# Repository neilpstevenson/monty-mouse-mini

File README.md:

# monty-mouse-mini
Source code for micromouse Monty Mini

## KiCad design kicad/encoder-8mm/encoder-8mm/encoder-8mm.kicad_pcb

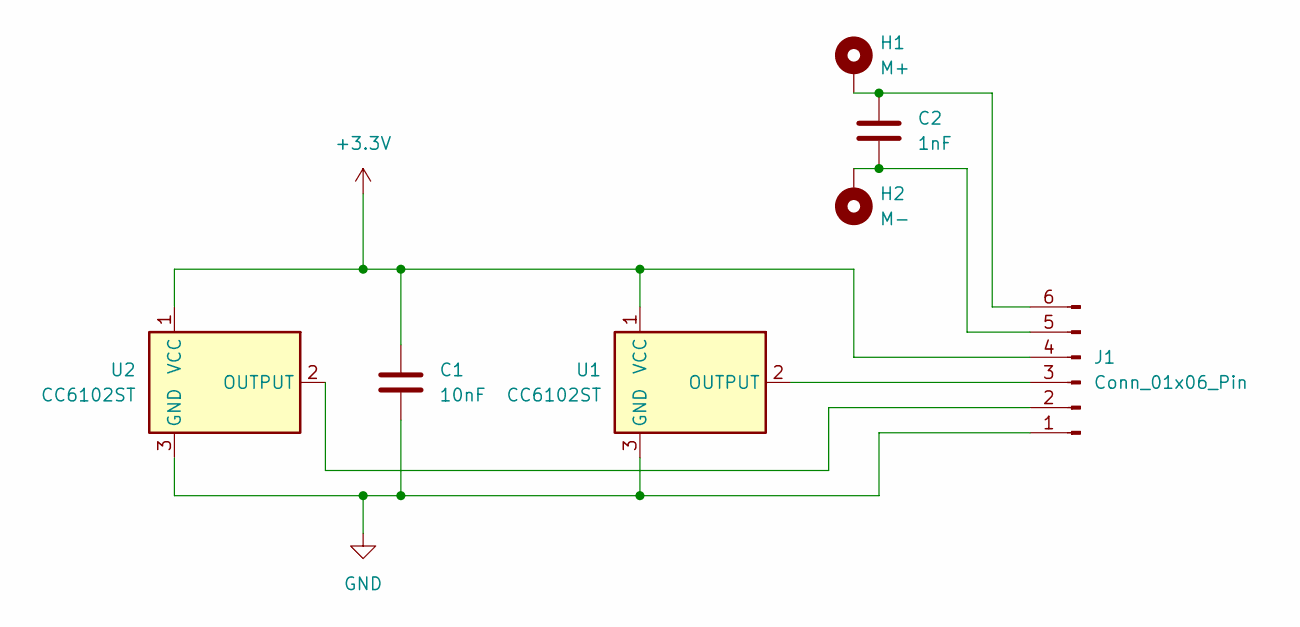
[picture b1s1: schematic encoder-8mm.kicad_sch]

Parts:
C1: 10nF; C_0805_2012Metric
C2: 1nF; C_0805_2012Metric
H1: M+; small_slot_1.2x0.3mm
H2: M-; small_slot_1.2x0.3mm
J1: Conn_01x06_Pin; PinSocket_1x06_P1.00mm_Vertical
U1, U2: CC6102ST; SOT-23

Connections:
+3.3V: C1.1, J1.4, U1.1 (VCC), U2.1 (VCC)
GND: C1.2, J1.1, U1.3 (GND), U2.3 (GND)
unnamed: J1.2, U2.2 (OUTPUT)
unnamed: J1.3, U1.2 (OUTPUT)
unnamed: C2.2, H2.1, J1.5
unnamed: C2.1, H1.1, J1.6

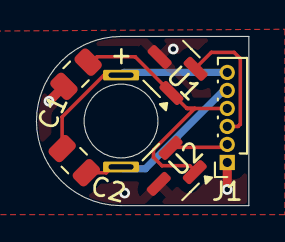
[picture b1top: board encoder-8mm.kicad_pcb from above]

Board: 2 copper layers, 11.8 x 9.4 mm, 7 parts (0 on the bottom side), 6 nets.

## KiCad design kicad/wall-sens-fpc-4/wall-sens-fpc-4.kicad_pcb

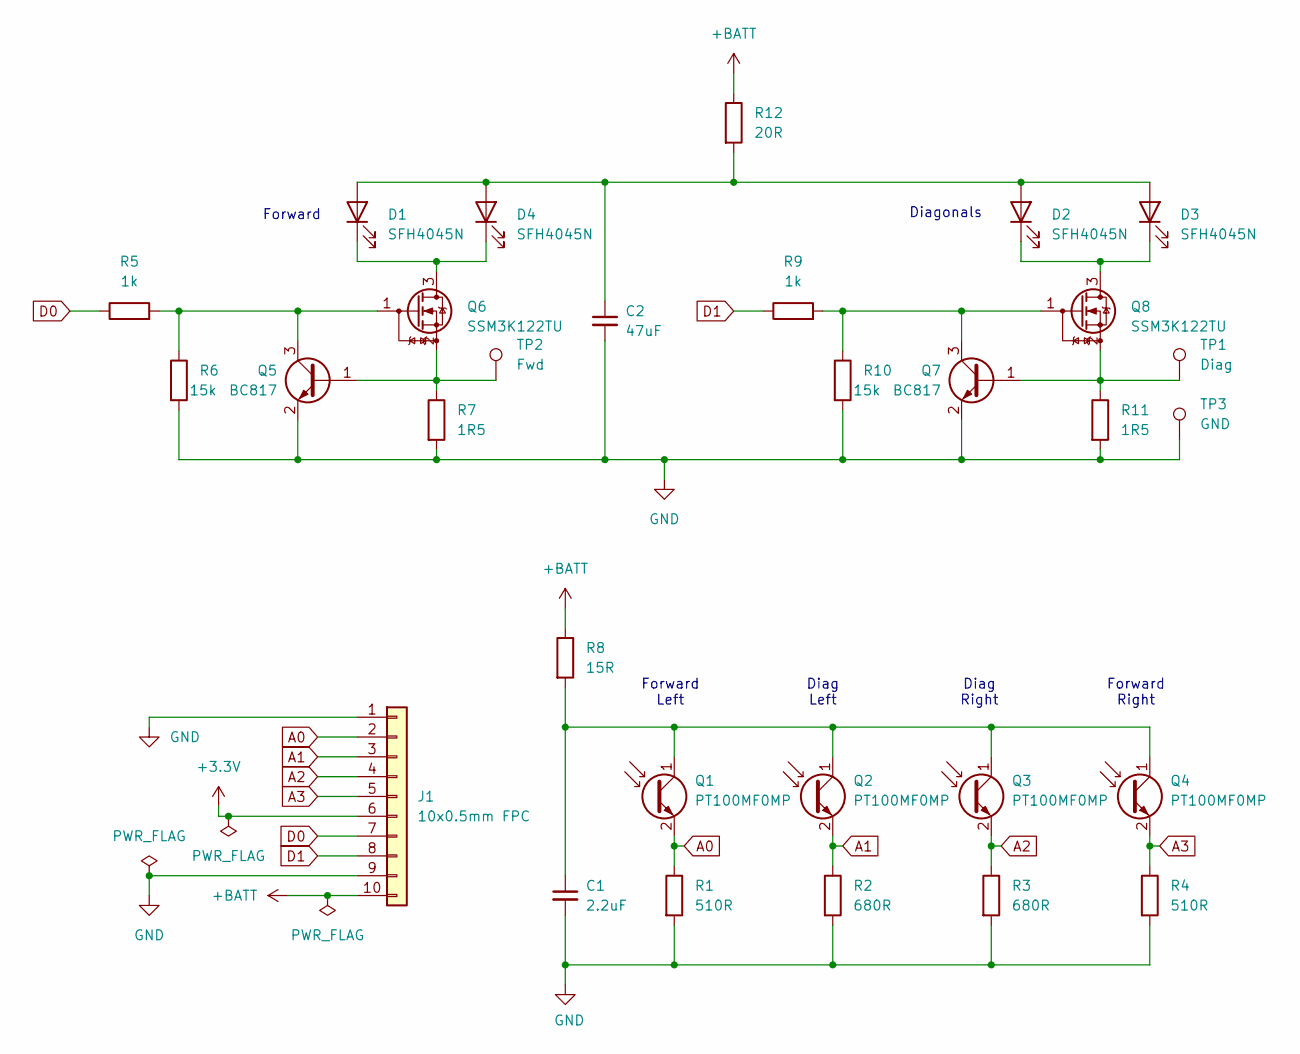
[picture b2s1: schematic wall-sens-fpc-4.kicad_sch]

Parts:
C1: 2.2uF; C_0805_2012Metric
C2: 47uF; C_1206_3216Metric
D1, D2, D3, D4: SFH4045N; LED_SFH_4045N
J1: 10x0.5mm FPC; SlimFPC_1x10-1MP_P0.5mm_Horizontal_ExtPads
Q1, Q2, Q3, Q4: PT100MF0MP; PT100_SHP_H
Q5, Q7: BC817; SOT-23
Q6, Q8: SSM3K122TU; UFM_TOS-M
R1, R4: 510R; R_0805_2012Metric
R2, R3: 680R; R_0805_2012Metric
R5, R9: 1k; R_0805_2012Metric
R6, R10: 15k; R_0805_2012Metric
R7, R11: 1R5; R_0805_2012Metric
R8: 15R; R_0805_2012Metric
R12: 20R; R_0805_2012Metric
TP1: Diag; TestPoint_Pad_D1.5mm
TP2: Fwd; TestPoint_Pad_D1.5mm
TP3: GND; TestPoint_THTPad_1.5x1.5mm_Drill0.7mm

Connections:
+3.3V: J1.6
+BATT: J1.10, R8.1, R12.1
A0: J1.2, Q1.2 (E), R1.1
A1: J1.3, Q2.2 (E), R2.1
A2: J1.4, Q3.2 (E), R3.1
A3: J1.5, Q4.2 (E), R4.1
D0: J1.7, R5.1
D1: J1.8, R9.1
GND: C1.2, C2.2, J1.1, J1.9, Q5.2 (E), Q7.2 (E), R1.2, R2.2, R3.2, R4.2, R6.2, R7.2, R10.2, R11.2, TP3.1
unnamed: C2.1, D1.2 (A), D2.2 (A), D3.2 (A), D4.2 (A), R12.2
unnamed: D1.1 (K), D4.1 (K), Q6.3 (D)
unnamed: D2.1 (K), D3.1 (K), Q8.3 (D)
unnamed: C1.1, Q1.1 (C), Q2.1 (C), Q3.1 (C), Q4.1 (C), R8.2
unnamed: Q5.1 (B), Q6.2 (S), R7.1, TP2.1
unnamed: Q5.3 (C), Q6.1 (G), R5.2, R6.1
unnamed: Q7.1 (B), Q8.2 (S), R11.1, TP1.1
unnamed: Q7.3 (C), Q8.1 (G), R9.2, R10.1

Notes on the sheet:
Forward Left
Diag Right
Diag Left
Diagonals
Forward
Forward Right

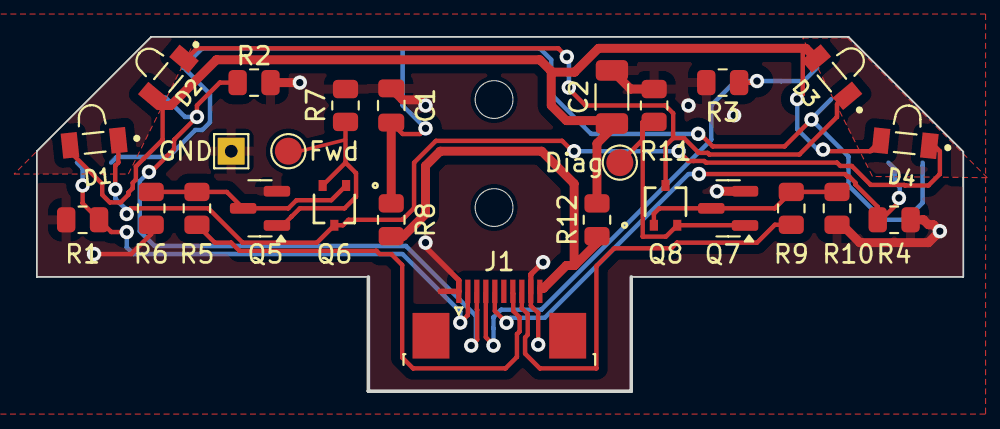
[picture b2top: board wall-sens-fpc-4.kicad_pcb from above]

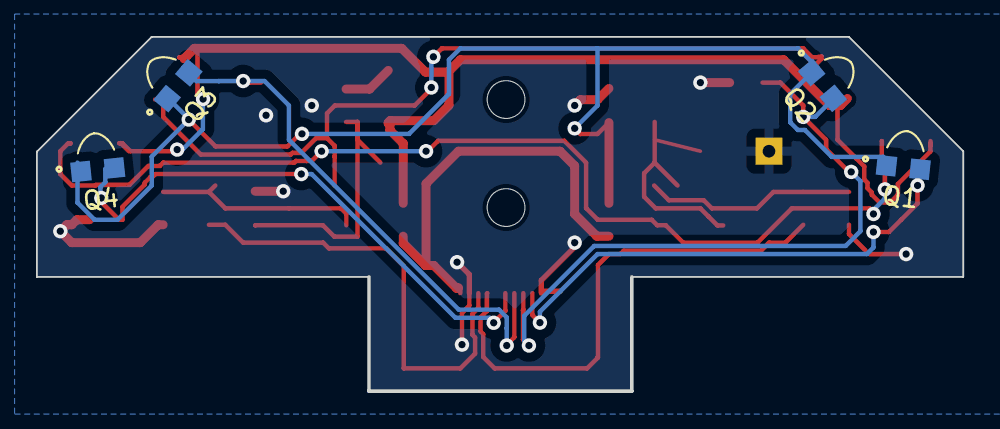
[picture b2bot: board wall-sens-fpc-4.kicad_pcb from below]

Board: 2 copper layers, 51.4 x 19.6 mm, 32 parts (4 on the bottom side), 16 nets.

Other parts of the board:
REF-mh: MountingHole_2.1mm
REF-mh#2: MountingHole_2.1mm

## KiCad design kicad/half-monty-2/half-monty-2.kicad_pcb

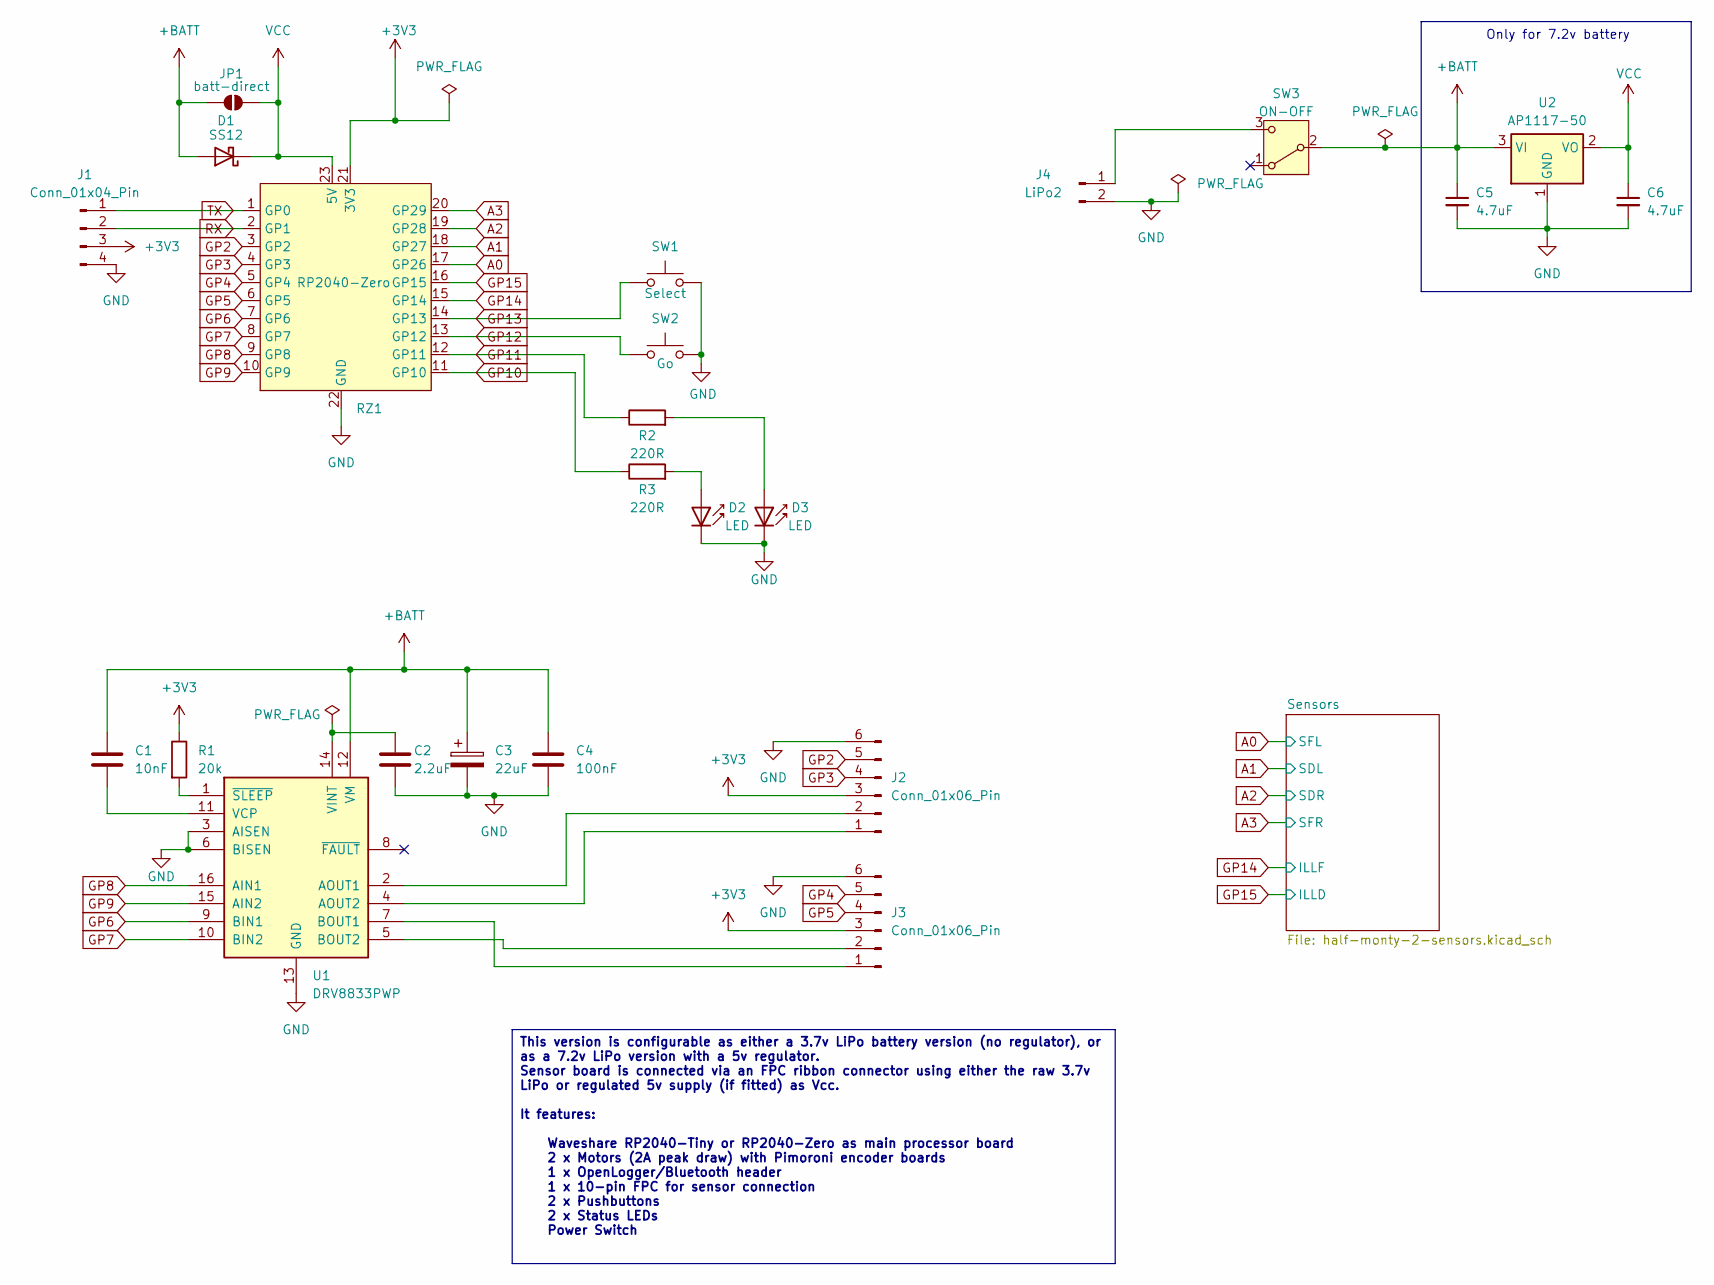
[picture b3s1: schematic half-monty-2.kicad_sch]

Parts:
C1: 10nF; C_0805_2012Metric
C2: 2.2uF; C_0805_2012Metric
C3: 22uF; C_0805_2012Metric
C4: 100nF; C_0805_2012Metric
C5, C6: 4.7uF; C_0805_2012Metric_Pad1.18x1.45mm_HandSolder
D1: SS12; D_SMA
D2, D3: LED; LED_1206_3216Metric
J1: Conn_01x04_Pin; PinHeader_1x04_P2.54mm_Vertical
J2, J3: Conn_01x06_Pin; JST_SH_SM06B-SRSS-TB_1x06-1MP_P1.00mm_Horizontal
J4: LiPo2; PinHeader_1x02_P1.27mm_Vertical
JP1: batt-direct; SolderJumper-2_P1.3mm_Open_Pad1.0x1.5mm
R1: 20k; R_0805_2012Metric
R2, R3: 220R; R_0805_2012Metric
RZ1: RP2040-Zero; RP2040-Zero-outline-THP
SW1: Select; SW_SPST_CK_RS282G05A3
SW2: Go; SW_SPST_CK_RS282G05A3
SW3: ON-OFF; SW_SPDT_PCM12_VERT
U1: DRV8833PWP; HTSSOP-16-1EP_4.4x5mm_P0.65mm_EP3.4x5mm_Mask2.46x2.31mm_The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
U2: AP1117-50; SOT-223-3_TabPin2

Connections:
+3V3: J1.3, J2.3, J3.3, R1.1, RZ1.21 (3V3)
+BATT: C1.1, C3.1, C4.1, C5.1, D1.2 (A), JP1.1 (A), SW3.2 (B), U1.12 (VM), U2.3 (VI); also elsewhere on the board
A0: RZ1.17 (GP26); also elsewhere on the board
A1: RZ1.18 (GP27); also elsewhere on the board
A2: RZ1.19 (GP28); also elsewhere on the board
A3: RZ1.20 (GP29); also elsewhere on the board
GND: C2.1, C3.2, C4.2, C5.2, C6.2, D2.1 (K), D3.1 (K), J1.4, J2.6, J3.6, J4.2, RZ1.22 (GND), SW1.2, SW2.2, U1.3 (AISEN), U1.6 (BISEN), U1.13 (GND), U1.17 (GND), U2.1 (GND); also elsewhere on the board
GP2: J2.5, RZ1.3 (GP2)
GP3: J2.4, RZ1.4 (GP3)
GP4: J3.5, RZ1.5 (GP4)
GP5: J3.4, RZ1.6 (GP5)
GP6: RZ1.7 (GP6), U1.9 (BIN1)
GP7: RZ1.8 (GP7), U1.10 (BIN2)
GP8: RZ1.9 (GP8), U1.16 (AIN1)
GP9: RZ1.10 (GP9), U1.15 (AIN2)
GP10: R3.1, RZ1.11 (GP10)
GP11: R2.1, RZ1.12 (GP11)
GP12: RZ1.13 (GP12), SW2.1
GP13: RZ1.14 (GP13), SW1.1
GP14: RZ1.15 (GP14); also elsewhere on the board
GP15: RZ1.16 (GP15); also elsewhere on the board
unnamed: D2.2 (A), R3.2
unnamed: D3.2 (A), R2.2
unnamed: J2.1, U1.4 (AOUT2)
unnamed: J2.2, U1.2 (AOUT1)
unnamed: J3.1, U1.7 (BOUT1)
unnamed: J3.2, U1.5 (BOUT2)
unnamed: J4.1, SW3.3 (C)
unnamed: C1.2, U1.11 (VCP)
unnamed: C2.2, U1.14 (VINT)
unnamed: R1.2, U1.1 (~SLEEP)
RX: J1.2, RZ1.2 (GP1)
TX: J1.1, RZ1.1 (GP0)
VCC: C6.1, D1.1 (K), JP1.2 (B), RZ1.23 (5V), U2.2 (VO)

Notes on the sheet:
Only for 7.2v battery
This version is configurable as either a 3.7v LiPo battery version (no regulator), or as a 7.2v LiPo version with a 5v regulator. Sensor board is connected via an FPC ribbon connector using either the raw 3.7v LiPo or regulated 5v supply (if fitted) as Vcc. It features: Waveshare RP2040-Tiny or RP2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

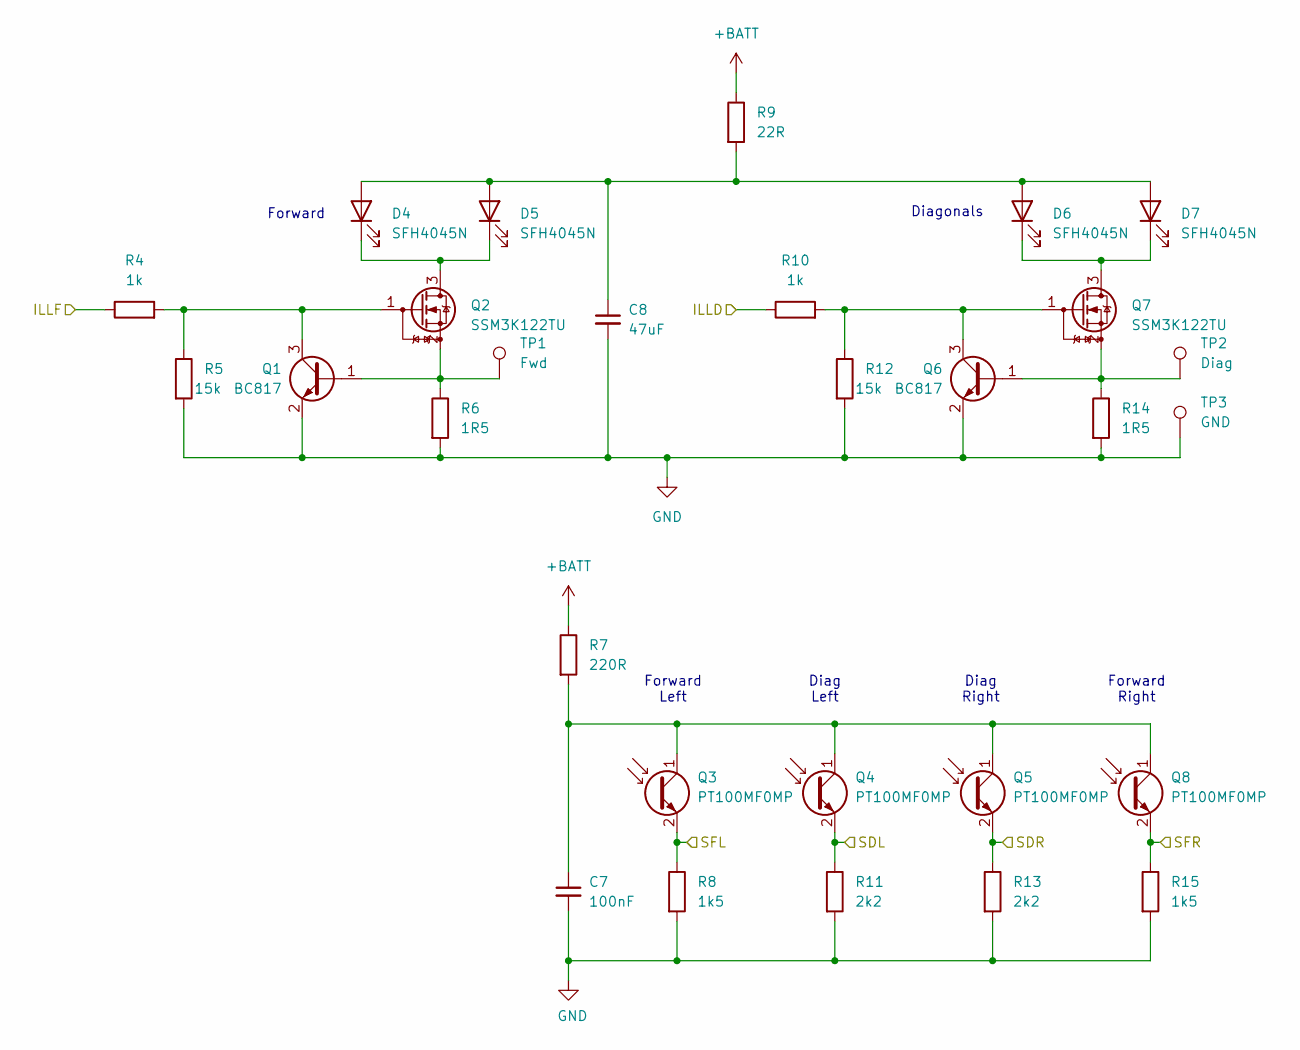
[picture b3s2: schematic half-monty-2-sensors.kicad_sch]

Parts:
C7: 100nF; C_0805_2012Metric
C8: 47uF; C_1206_3216Metric
D4, D5, D6, D7: SFH4045N; LED_SFH_4045N
Q1, Q6: BC817; SOT-23
Q2, Q7: SSM3K122TU; UFM_TOS-M
Q3, Q4, Q5, Q8: PT100MF0MP; PT100_SHP_H
R4, R10: 1k; R_0805_2012Metric
R5, R12: 15k; R_0805_2012Metric
R6, R14: 1R5; R_0805_2012Metric
R7: 220R; R_0805_2012Metric
R8, R15: 1k5; R_0805_2012Metric
R9: 22R; R_0805_2012Metric
R11, R13: 2k2; R_0805_2012Metric
TP1: Fwd; TestPoint_Pad_D1.5mm
TP2: Diag; TestPoint_Pad_D1.5mm
TP3: GND; TestPoint_THTPad_1.5x1.5mm_Drill0.7mm

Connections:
+BATT: R7.1, R9.1; also elsewhere on the board
A0: Q3.2 (E), R8.1; also elsewhere on the board
A1: Q4.2 (E), R11.1; also elsewhere on the board
A2: Q5.2 (E), R13.1; also elsewhere on the board
A3: Q8.2 (E), R15.1; also elsewhere on the board
GND: C7.2, C8.2, Q1.2 (E), Q6.2 (E), R5.2, R6.2, R8.2, R11.2, R12.2, R13.2, R14.2, R15.2, TP3.1; also elsewhere on the board
GP14: R4.1; also elsewhere on the board
GP15: R10.1; also elsewhere on the board
unnamed: C8.1, D4.2 (A), D5.2 (A), D6.2 (A), D7.2 (A), R9.2
unnamed: D4.1 (K), D5.1 (K), Q2.3 (D)
unnamed: D6.1 (K), D7.1 (K), Q7.3 (D)
unnamed: Q1.1 (B), Q2.2 (S), R6.1, TP1.1
unnamed: Q1.3 (C), Q2.1 (G), R4.2, R5.1
unnamed: C7.1, Q3.1 (C), Q4.1 (C), Q5.1 (C), Q8.1 (C), R7.2
unnamed: Q6.1 (B), Q7.2 (S), R14.1, TP2.1
unnamed: Q6.3 (C), Q7.1 (G), R10.2, R12.1

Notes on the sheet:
Diagonals
Forward
Forward Left
Diag Right
Forward Right
Diag Left

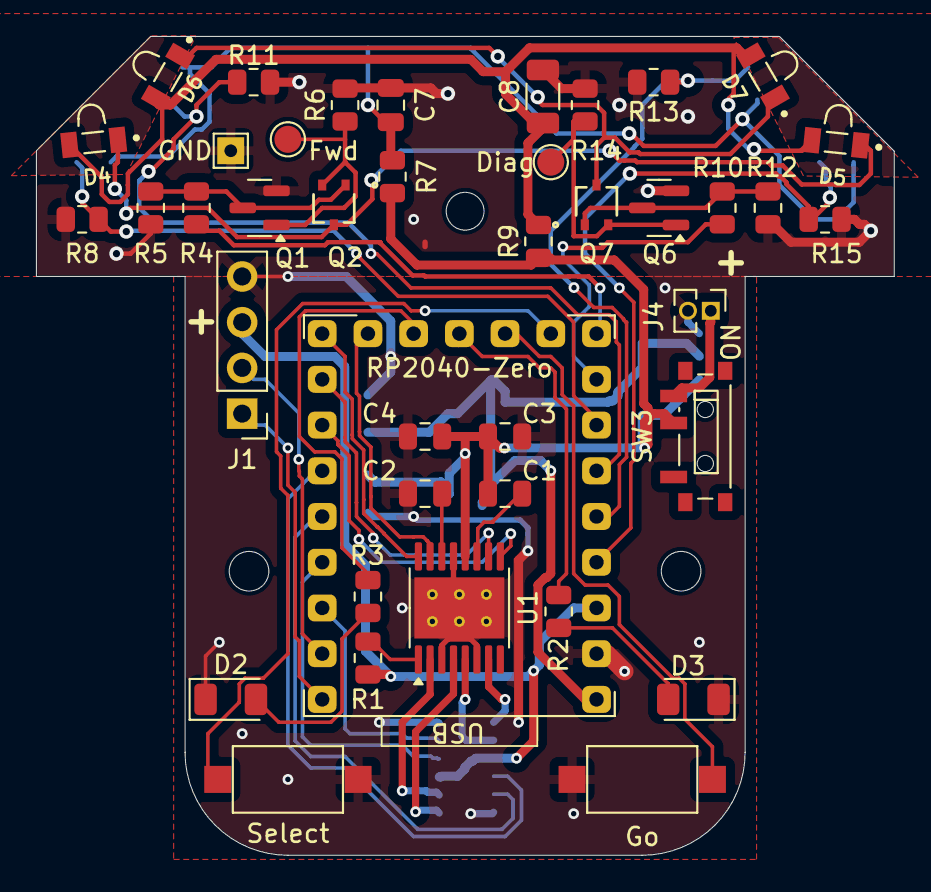
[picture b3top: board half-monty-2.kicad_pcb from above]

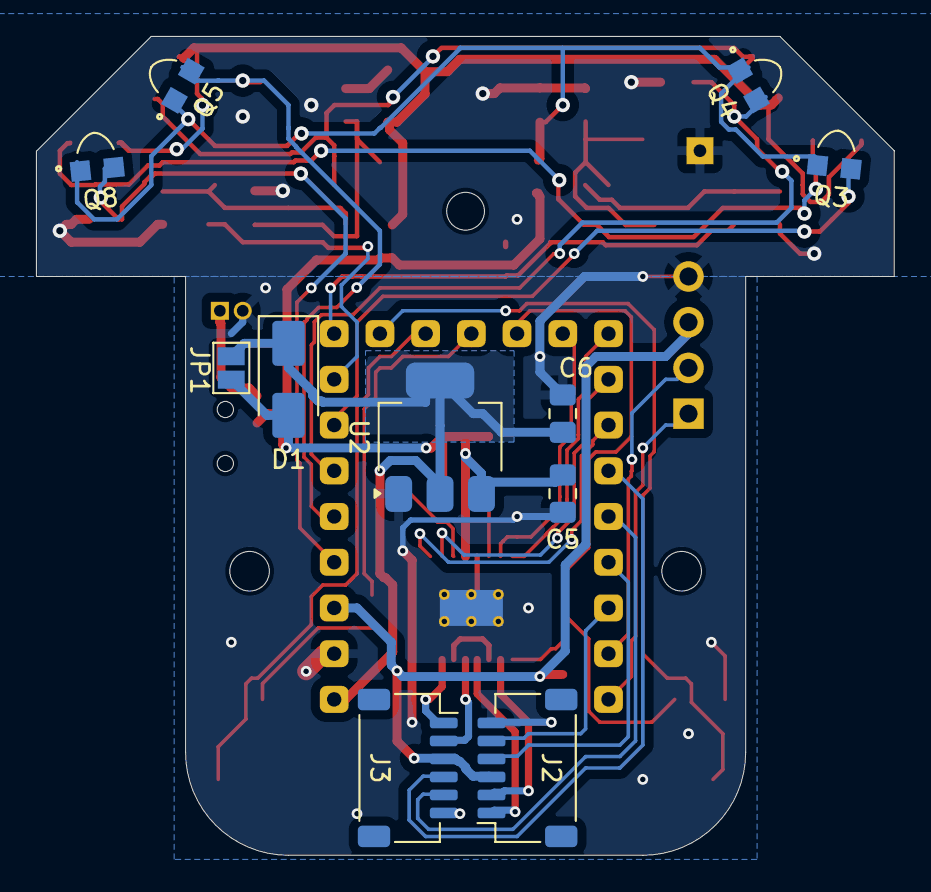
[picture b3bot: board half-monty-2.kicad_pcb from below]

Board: 2 copper layers, 47.7 x 45.5 mm, 53 parts (11 on the bottom side), 42 nets.

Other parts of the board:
REF-mh: MountingHole_2.1mm

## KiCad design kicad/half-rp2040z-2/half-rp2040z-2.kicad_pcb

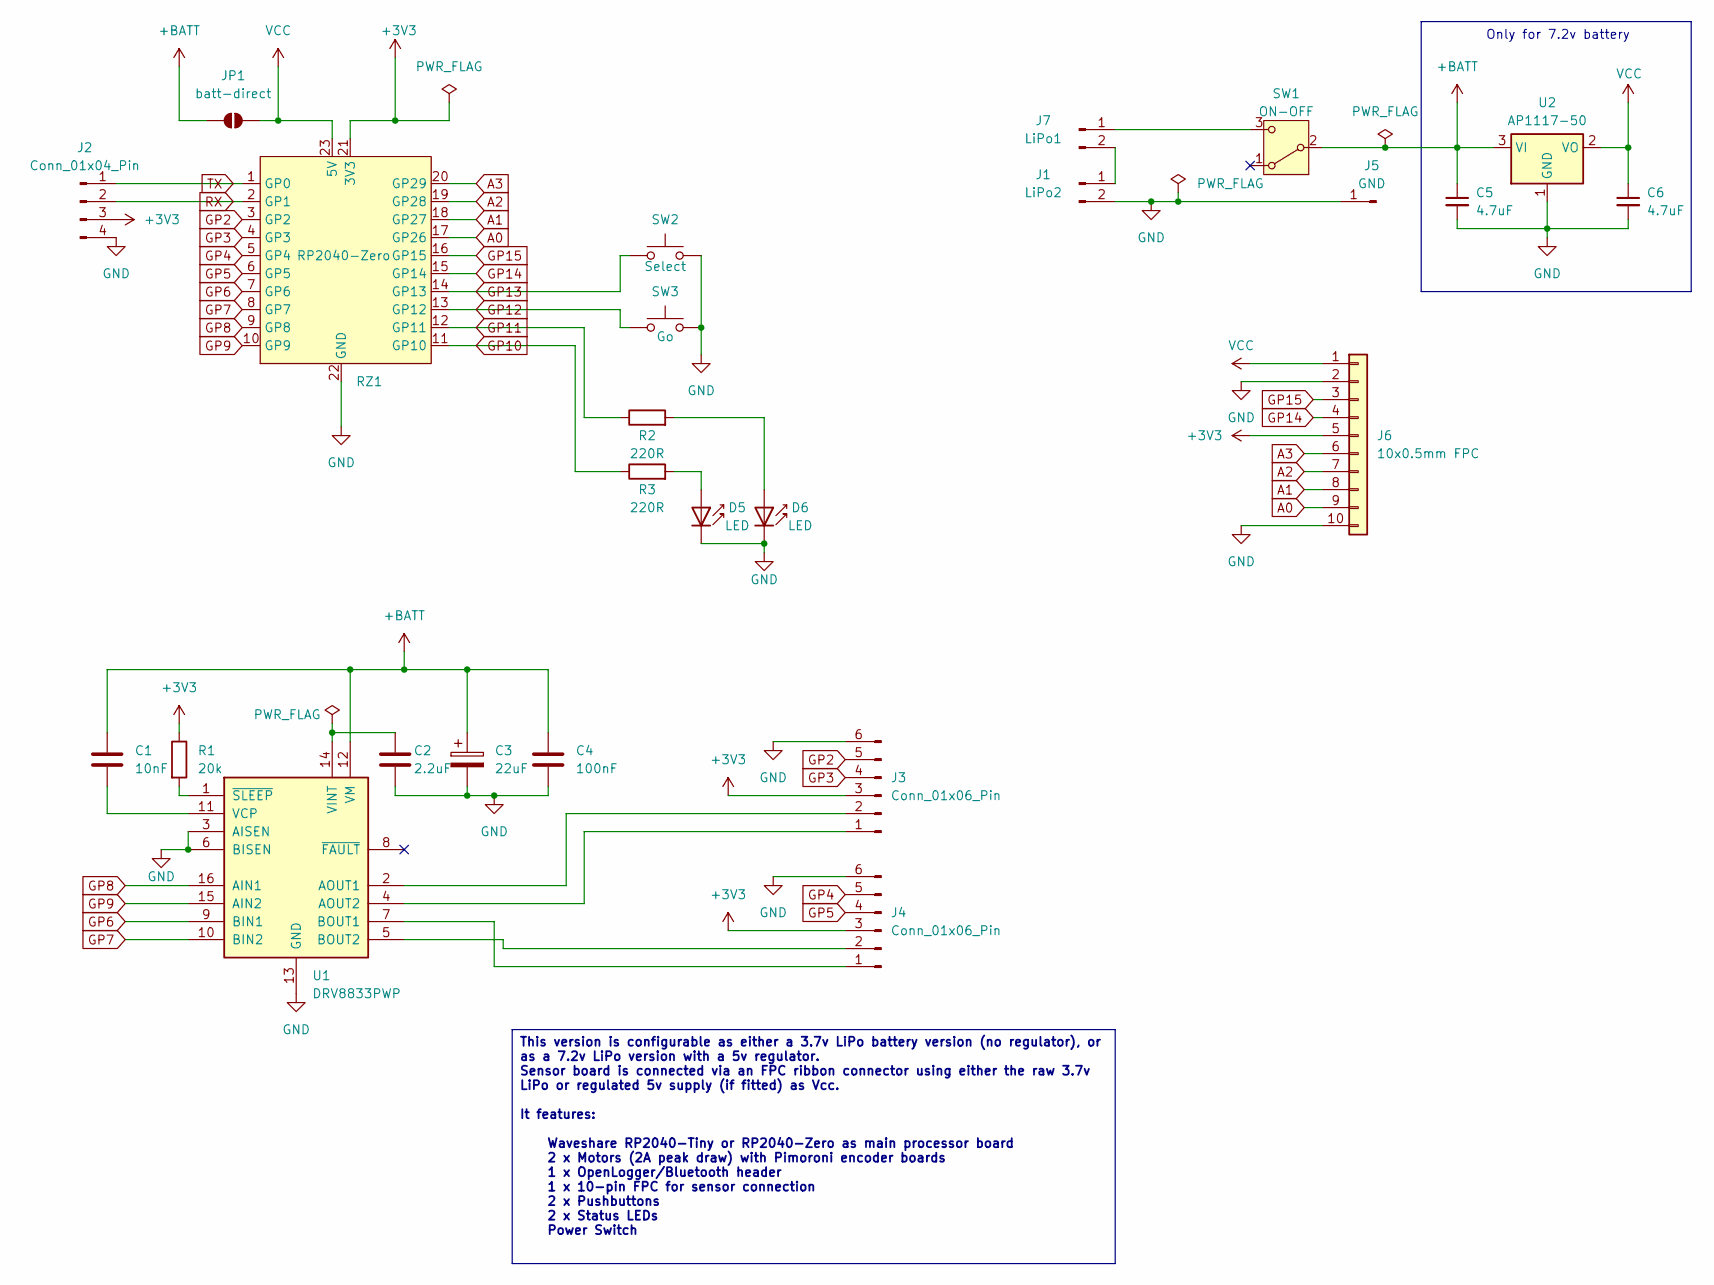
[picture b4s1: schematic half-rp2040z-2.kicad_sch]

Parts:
C1: 10nF; C_0805_2012Metric
C2: 2.2uF; C_0805_2012Metric
C3: 22uF; C_0805_2012Metric
C4: 100nF; C_0805_2012Metric
C5, C6: 4.7uF; C_0805_2012Metric_Pad1.18x1.45mm_HandSolder
D5, D6: LED; LED_1206_3216Metric
J1: LiPo2; PinHeader_1x02_P1.27mm_Vertical
J2: Conn_01x04_Pin; PinHeader_1x04_P2.54mm_Vertical
J3, J4: Conn_01x06_Pin; JST_SH_SM06B-SRSS-TB_1x06-1MP_P1.00mm_Horizontal
J5: GND; PinHeader_1x01_P2.54mm_Vertical
J6: 10x0.5mm FPC; SlimFPC_1x10-1MP_P0.5mm_Horizontal_ExtPads
J7: LiPo1; PinHeader_1x02_P1.27mm_Vertical
JP1: batt-direct; SolderJumper-2_P1.3mm_Open_Pad1.0x1.5mm
R1: 20k; R_0805_2012Metric
R2, R3: 220R; R_0805_2012Metric
RZ1: RP2040-Zero; RP2040-Zero-outline-THP
SW1: ON-OFF; SW_SPDT_PCM12_VERT
SW2: Select; SW_SPST_CK_RS282G05A3
SW3: Go; SW_SPST_CK_RS282G05A3
U1: DRV8833PWP; HTSSOP-16-1EP_4.4x5mm_P0.65mm_EP3.4x5mm_Mask2.46x2.31mm_The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
U2: AP1117-50; SOT-223-3_TabPin2

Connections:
+3V3: J2.3, J3.3, J4.3, J6.5, R1.1, RZ1.21 (3V3)
+BATT: C1.1, C3.1, C4.1, C5.1, JP1.1 (A), SW1.2 (B), U1.12 (VM), U2.3 (VI)
A0: J6.9, RZ1.17 (GP26)
A1: J6.8, RZ1.18 (GP27)
A2: J6.7, RZ1.19 (GP28)
A3: J6.6, RZ1.20 (GP29)
GND: C2.1, C3.2, C4.2, C5.2, C6.2, D5.1 (K), D6.1 (K), J1.2, J2.4, J3.6, J4.6, J5.1, J6.2, J6.10, RZ1.22 (GND), SW2.2, SW3.2, U1.3 (AISEN), U1.6 (BISEN), U1.13 (GND), U1.17 (GND), U2.1 (GND)
GP2: J3.5, RZ1.3 (GP2)
GP3: J3.4, RZ1.4 (GP3)
GP4: J4.5, RZ1.5 (GP4)
GP5: J4.4, RZ1.6 (GP5)
GP6: RZ1.7 (GP6), U1.9 (BIN1)
GP7: RZ1.8 (GP7), U1.10 (BIN2)
GP8: RZ1.9 (GP8), U1.16 (AIN1)
GP9: RZ1.10 (GP9), U1.15 (AIN2)
GP10: R3.1, RZ1.11 (GP10)
GP11: R2.1, RZ1.12 (GP11)
GP12: RZ1.13 (GP12), SW3.1
GP13: RZ1.14 (GP13), SW2.1
GP14: J6.4, RZ1.15 (GP14)
GP15: J6.3, RZ1.16 (GP15)
unnamed: D5.2 (A), R3.2
unnamed: D6.2 (A), R2.2
unnamed: J1.1, J7.2
unnamed: J3.1, U1.4 (AOUT2)
unnamed: J3.2, U1.2 (AOUT1)
unnamed: J4.1, U1.7 (BOUT1)
unnamed: J4.2, U1.5 (BOUT2)
unnamed: J7.1, SW1.3 (C)
unnamed: C1.2, U1.11 (VCP)
unnamed: C2.2, U1.14 (VINT)
unnamed: R1.2, U1.1 (~SLEEP)
RX: J2.2, RZ1.2 (GP1)
TX: J2.1, RZ1.1 (GP0)
VCC: C6.1, J6.1, JP1.2 (B), RZ1.23 (5V), U2.2 (VO)

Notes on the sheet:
Only for 7.2v battery
This version is configurable as either a 3.7v LiPo battery version (no regulator), or as a 7.2v LiPo version with a 5v regulator. Sensor board is connected via an FPC ribbon connector using either the raw 3.7v LiPo or regulated 5v supply (if fitted) as Vcc. It features: Waveshare RP2040-Tiny or RP2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

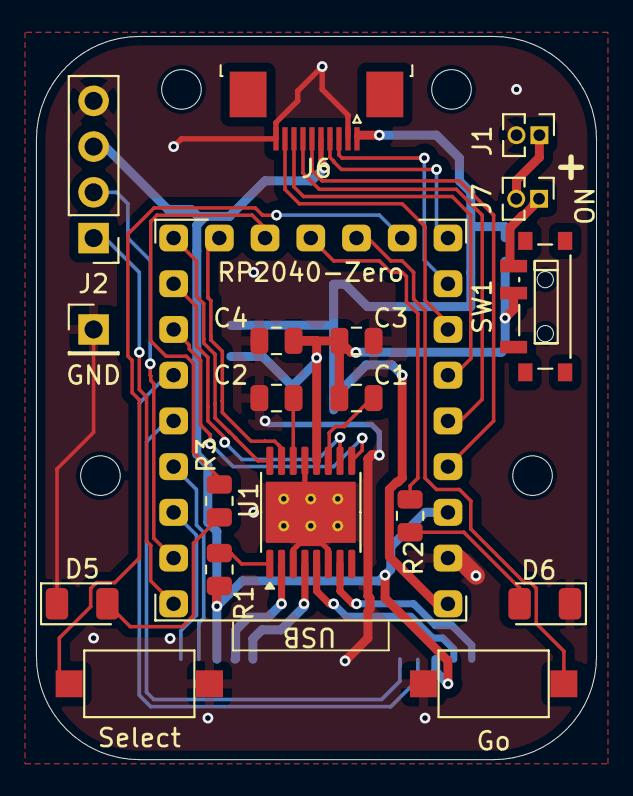
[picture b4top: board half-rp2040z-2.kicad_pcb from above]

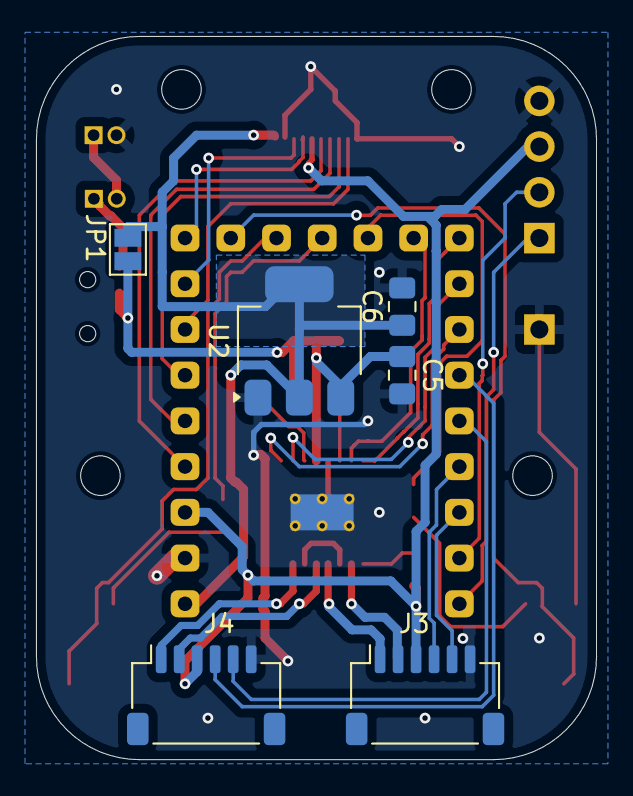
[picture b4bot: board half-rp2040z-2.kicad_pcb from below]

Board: 2 copper layers, 31.1 x 40.2 mm, 25 parts (6 on the bottom side), 35 nets.

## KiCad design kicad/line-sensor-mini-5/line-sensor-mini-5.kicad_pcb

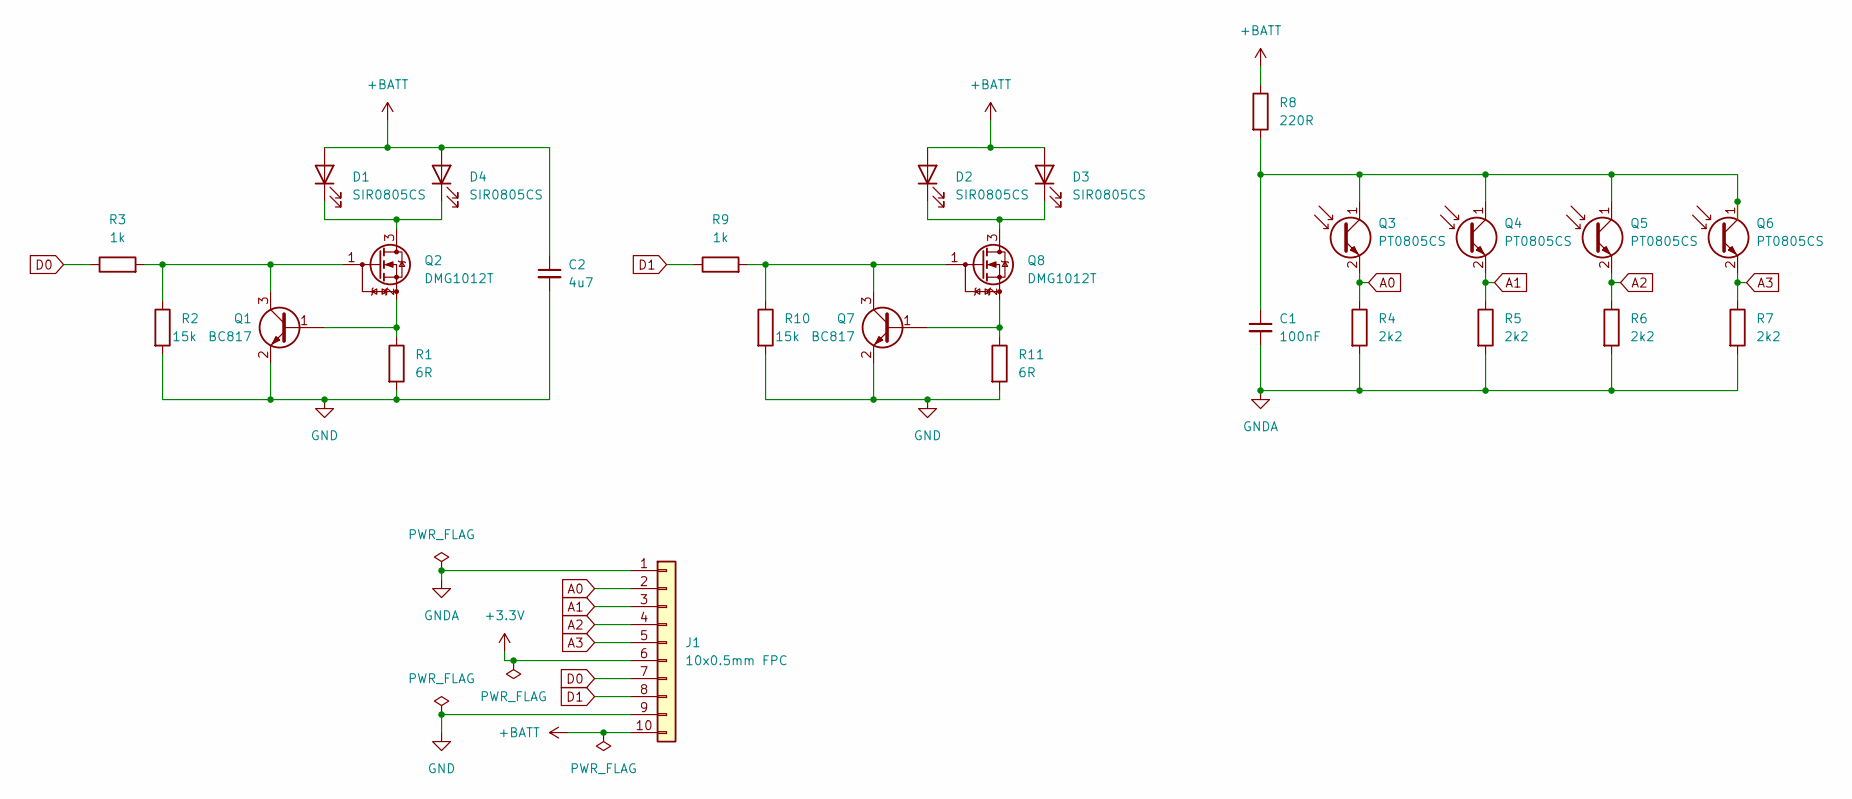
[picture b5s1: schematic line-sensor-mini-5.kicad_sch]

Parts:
C1: 100nF; C_0805_2012Metric
C2: 4u7; C_0805_2012Metric
D1, D2, D3, D4: SIR0805CS; LED_0805_2012Metric_Pad1.15x1.40mm_HandSolder
J1: 10x0.5mm FPC; TE_1-1734839-0_1x10-1MP_P0.5mm_Horizontal
Q1, Q7: BC817; SOT-23
Q2, Q8: DMG1012T; SOT-523
Q3, Q4, Q5, Q6: PT0805CS; LED_0805_2012Metric_Pad1.15x1.40mm_HandSolder
R1, R11: 6R; R_0805_2012Metric
R2, R10: 15k; R_0805_2012Metric
R3, R9: 1k; R_0805_2012Metric
R4, R5, R6, R7: 2k2; R_0805_2012Metric
R8: 220R; R_0805_2012Metric

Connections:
+3.3V: J1.6
+BATT: C2.1, D1.2 (A), D2.2 (A), D3.2 (A), D4.2 (A), J1.10, R8.1
A0: J1.2, Q3.2 (E), R4.1
A1: J1.3, Q4.2 (E), R5.1
A2: J1.4, Q5.2 (E), R6.1
A3: J1.5, Q6.2 (E), R7.1
D0: J1.7, R3.1
D1: J1.8, R9.1
GND: C2.2, J1.9, Q1.2 (E), Q7.2 (E), R1.2, R2.2, R10.2, R11.2
GNDA: C1.2, J1.1, R4.2, R5.2, R6.2, R7.2
unnamed: D1.1 (K), D4.1 (K), Q2.3 (D)
unnamed: D2.1 (K), D3.1 (K), Q8.3 (D)
unnamed: Q1.1 (B), Q2.2 (S), R1.1
unnamed: Q1.3 (C), Q2.1 (G), R2.1, R3.2
unnamed: C1.1, Q3.1 (C), Q4.1 (C), Q5.1 (C), Q6.1 (C), R8.2
unnamed: Q7.1 (B), Q8.2 (S), R11.1
unnamed: Q7.3 (C), Q8.1 (G), R9.2, R10.1

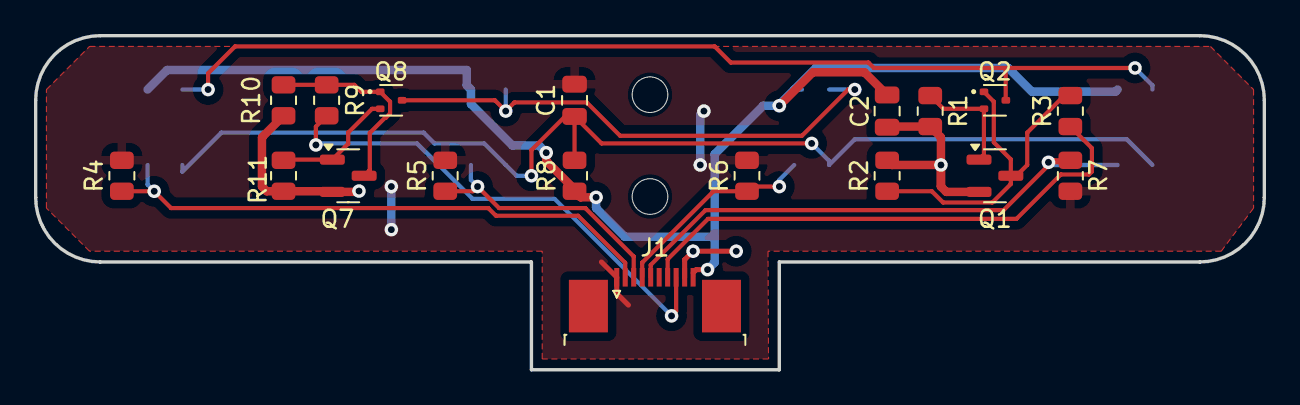
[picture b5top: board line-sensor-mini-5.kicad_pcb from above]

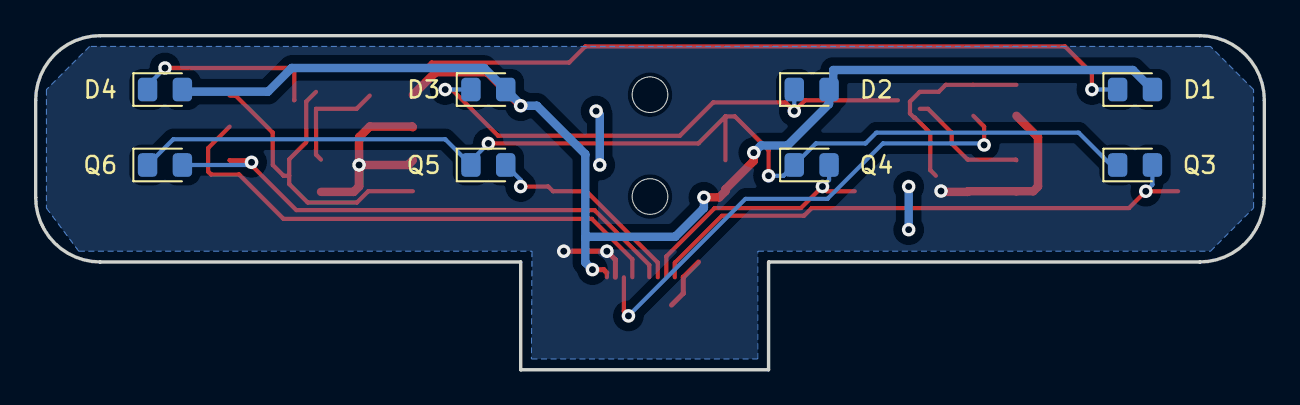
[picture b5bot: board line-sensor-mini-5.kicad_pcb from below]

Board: 2 copper layers, 72.4 x 19.7 mm, 28 parts (8 on the bottom side), 16 nets.

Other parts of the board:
REF-mh: MountingHole_2.1mm
REF-mh#2: MountingHole_2.1mm

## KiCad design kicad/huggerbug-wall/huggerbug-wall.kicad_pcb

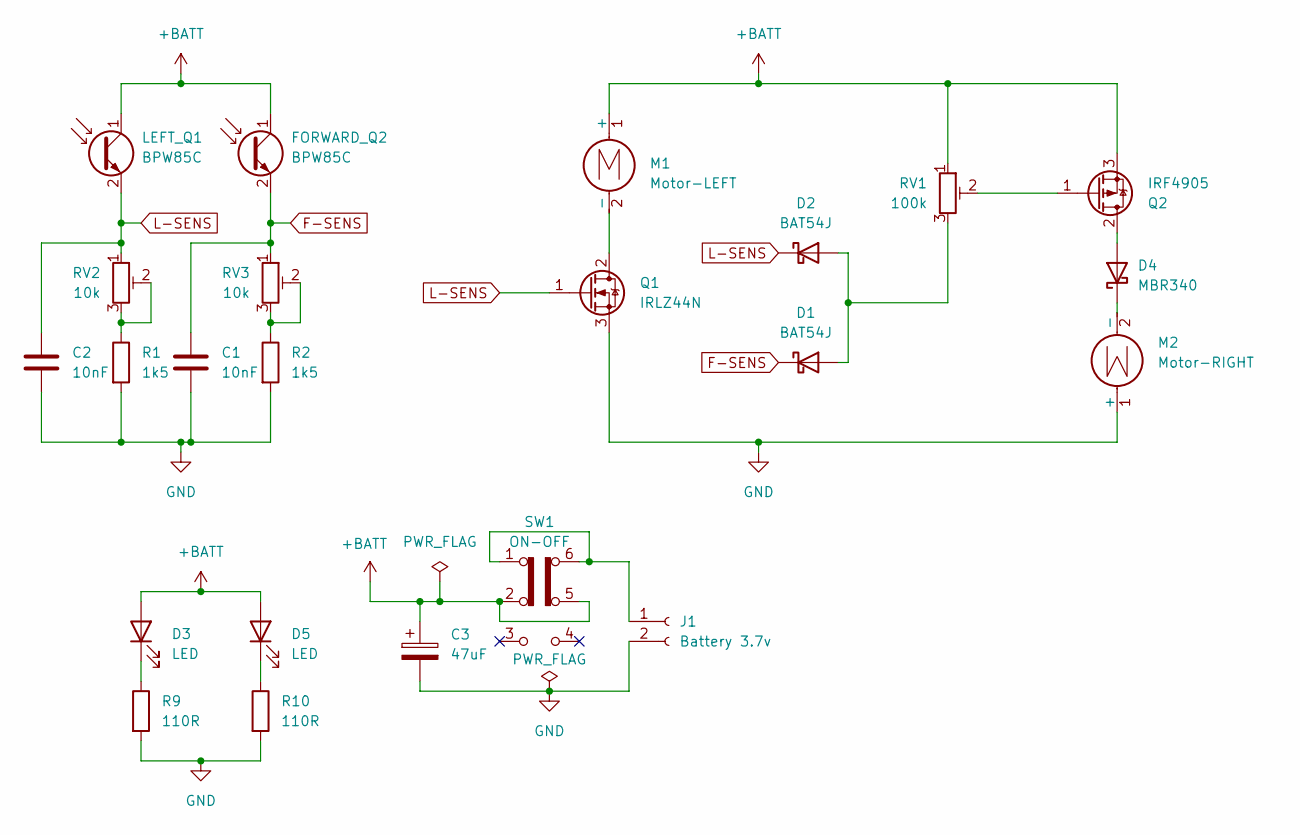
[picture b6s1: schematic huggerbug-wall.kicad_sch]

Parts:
C1, C2: 10nF; C_0805_2012Metric
C3: 47uF; C_1206_3216Metric
D1, D2: BAT54J; D_SOD-323F
D3, D5: LED; LED_D5.0mm
D4: MBR340; D_SMA
FORWARD_Q2: BPW85C; LED_D3.0mm_Clear
J1: Battery 3.7v; JST_PH_B2B-PH-K_1x02_P2.00mm_Vertical
LEFT_Q1: BPW85C; LED_D3.0mm_Clear
M1: Motor-LEFT; PinHeader_1x02_P1.27mm_Vertical
M2: Motor-RIGHT; PinHeader_1x02_P1.27mm_Vertical
Q1: IRLZ44N; TO-252-2
Q2: IRF4905; TO-252-2
R1, R2: 1k5; R_0805_2012Metric
R9, R10: 110R; R_0805_2012Metric
RV1: 100k; Potentiometer_Bourns_TC33X_Vertical
RV2, RV3: 10k; Potentiometer_Bourns_TC33X_Vertical
SW1: ON-OFF; PinHeader_2x03_P2.54mm_Vertical_SMD

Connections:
+BATT: C3.1, D3.2 (A), D5.2 (A), FORWARD_Q2.1 (C), LEFT_Q1.1 (C), M1.1 (+), Q2.3 (S), RV1.1, SW1.2 (B), SW1.5 (B)
F-SENS: C1.1, D1.1 (K), FORWARD_Q2.2 (E), RV3.1
GND: C1.2, C2.2, C3.2, J1.2, M2.1 (+), Q1.3 (S), R1.2, R2.2, R9.2, R10.2
L-SENS: C2.1, D2.1 (K), LEFT_Q1.2 (E), Q1.1 (G), RV2.1
unnamed: D1.2 (A), D2.2 (A), RV1.3
unnamed: D3.1 (K), R9.1
unnamed: D4.2 (A), Q2.2 (D)
unnamed: D4.1 (K), M2.2 (-)
unnamed: D5.1 (K), R10.1
unnamed: J1.1, SW1.1 (A), SW1.6 (C)
unnamed: M1.2 (-), Q1.2 (D)
unnamed: Q2.1 (G), RV1.2
unnamed: R1.1, RV2.2, RV2.3
unnamed: R2.1, RV3.2, RV3.3
